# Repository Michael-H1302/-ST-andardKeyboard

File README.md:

A custom keyboard design made with KiCad. The Design uses a STM32 Blue Pill Microcontroller featuring red led backlight that can be controlled in three groups (two rows per group). Don't get confused by the name HotKeyBoard. I just made use of some previous work and derived it from an already existing KiCad project. 
The keyboard design supports standard mechanical switches like the Cherry MX and the Gateron. Due to the LED placement below the actual switch footprint, even switches without an
extra space for the LED are supported.

andardKeyboard.jpg)

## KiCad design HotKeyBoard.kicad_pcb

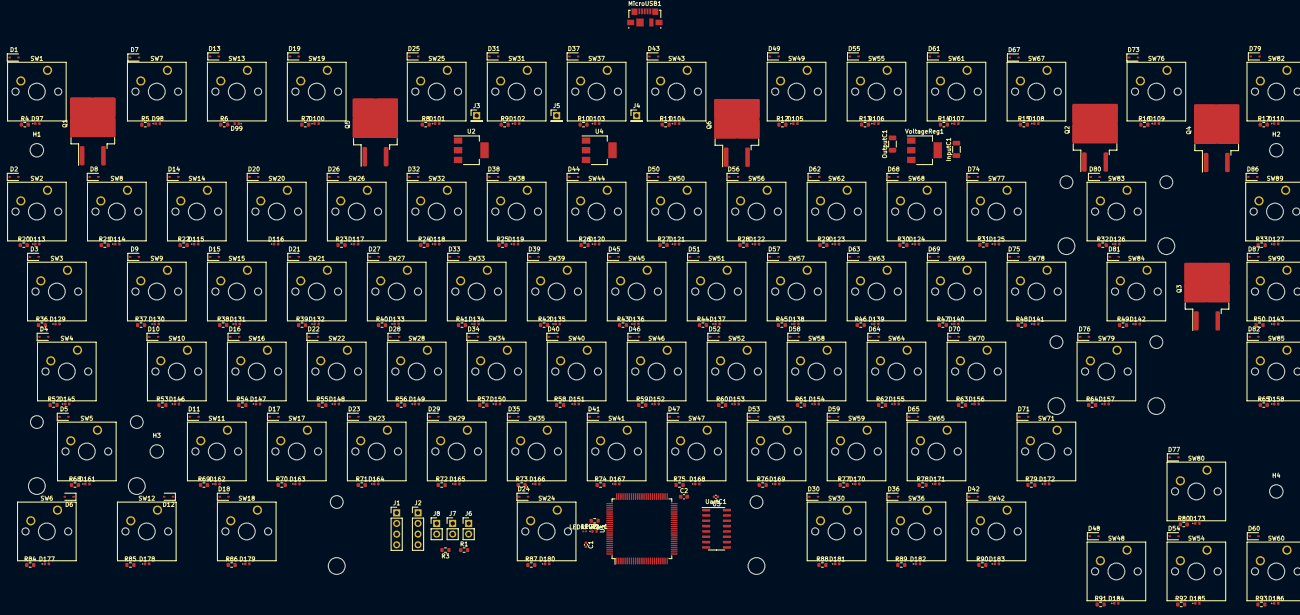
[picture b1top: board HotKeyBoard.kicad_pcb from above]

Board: 2 copper layers, 357 parts (0 on the bottom side), 211 nets, no tracks yet.

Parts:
C1: 0.1uF; C_0402_1005Metric
C2: 1uF; C_0603_1608Metric
D1, D2, D3, D4, D5, D6, D7, D8, D9, D10, D11, D12, D13, D14, D15, D16, D17, D18, D19, D20, D21, D22, D23, D24, D25, D26, D27, D28, D29, D30, D31, D32, D33, D34, D35, D36, D37, D38, D39, D40, D41, D42, D43, D44, D45, D46, D47, D48, D49, D50, D51, D52, D53, D54, D55, D56, D57, D58, D59, D60, D61, D62, D63, D64, D65, D67, D68, D69, D70, D71, D73, D74, D75, D76, D77, D79, D80, D81, D82, D86, D87: D; D_SOD-323
D97, D98, D99, D100, D101, D102, D103, D104, D105, D106, D107, D108, D109, D110, D113, D114, D115, D116, D117, D118, D119, D120, D121, D122, D123, D124, D125, D126, D127, D129, D130, D131, D132, D133, D134, D135, D136, D137, D138, D139, D140, D141, D142, D143, D145, D146, D147, D148, D149, D150, D151, D152, D153, D154, D155, D156, D157, D158, D161, D162, D163, D164, D165, D166, D167, D168, D169, D170, D171, D172, D173, D177, D178, D179, D180, D181, D182, D183, D184, D185, D186: LED; LED_0402_1005Metric
H1, H2, H3, H4: MountingHole; MountingHole_3.2mm_M3_DIN965
InputC1: 100uF; C_1206_3216Metric
J1, J2: Conn_01x04_Pin; PinHeader_1x04_P2.54mm_Vertical
J3: USB_VOLTAGE Measuring Point; PinHeader_1x01_P2.54mm_Vertical
J4: LED_VOLTAGE Measuring Point 1; PinHeader_1x01_P2.54mm_Vertical
J5: LED_VOLTAGE Measuring Point 2; PinHeader_1x01_P2.54mm_Vertical
J6, J7, J8: Conn_01x02_Pin; PinHeader_1x02_P2.54mm_Vertical
LEDPwr1: LED; LED_0402_1005Metric
LEDRPwr1: 65; R_0201_0603Metric
MicroUSB1: USB_OTG; USB_Micro-B_Molex_47346-0001
OutputC1: 100uF; C_1206_3216Metric
Q1, Q2, Q3, Q4, Q5, Q6: IRLZ34N; TO-263-2
R1, R2, R3: 10k; R_0603_1608Metric
R4, R5, R6, R7, R8, R9, R10, R11, R12, R13, R14, R15, R16, R17, R20, R21, R22, R23, R24, R25, R26, R27, R28, R29, R30, R31, R32, R33, R36, R37, R38, R39, R40, R41, R42, R43, R44, R45, R46, R47, R48, R49, R50, R52, R53, R54, R55, R56, R57, R58, R59, R60, R61, R62, R63, R64, R65, R68, R69, R70, R71, R72, R73, R74, R75, R76, R77, R78, R79, R80, R84, R85, R86, R87, R88, R89, R90, R91, R92, R93: R; R_0603_1608Metric
SW1, SW2, SW7, SW8, SW9, SW10, SW11, SW13, SW14, SW15, SW16, SW17, SW19, SW20, SW21, SW22, SW23, SW25, SW26, SW27, SW28, SW29, SW30, SW31, SW32, SW33, SW34, SW35, SW36, SW37, SW38, SW39, SW40, SW41, SW42, SW43, SW44, SW45, SW46, SW47, SW48, SW49, SW50, SW51, SW52, SW53, SW54, SW55, SW56, SW57, SW58, SW59, SW60, SW61, SW62, SW63, SW64, SW65, SW67, SW68, SW69, SW70, SW76, SW77, SW78, SW80, SW82, SW85, SW89, SW90: SW_Push; SW_Cherry_MX_1.00u_PCB
SW3, SW84: SW_Push; SW_Cherry_MX_1.50u_PCB
SW4, SW71: SW_Push; SW_Cherry_MX_1.75u_PCB
SW5, SW79: SW_Push; SW_Cherry_MX_2.25u_PCB
SW6, SW12, SW18: SW_Push; SW_Cherry_MX_1.25u_PCB
SW24: SW_Push; SW_Cherry_MX_6.25u_PCB
SW83: SW_Push; SW_Cherry_MX_2.00u_PCB
U1: STM32F103VBTx; LQFP-100_14x14mm_P0.5mm
U2, U4: AMS1117-3.3; SOT-223-3_TabPin2
U3: CH340C; SOIC-16_3.9x9.9mm_P1.27mm
UartC1: 0.1uF; C_0402_1005Metric
VoltageReg1: AMS1117-3.3; SOT-223-3_TabPin2

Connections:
3.3V: C1.2, C2.1, J1.4, J2.4, J7.1, LEDRPwr1.1, OutputC1.1, R1.1, R3.1, U1.6 (VBAT), U1.11 (VDD), U1.21 (VREF+), U1.22 (VDDA), U1.28 (VDD), U1.50 (VDD), U1.75 (VDD), U1.100 (VDD), U3.4 (V3), U3.16 (VCC), UartC1.2, VoltageReg1.2 (VO)
Boot0: J7.2, R2.1, U1.94 (BOOT0)
Boot1: J8.2, R3.2, U1.37 (PB2)
Col0: SW1.1, SW2.1, SW3.1, SW4.1, SW5.1, SW6.1, U1.81 (PD0)
Col1: SW7.1, SW8.1, SW9.1, SW10.1, SW11.1, SW12.1, U1.82 (PD1)
Col2: SW13.1, SW14.1, SW15.1, SW16.1, SW17.1, SW18.1, U1.83 (PD2)
Col3: SW19.1, SW20.1, SW21.1, SW22.1, SW23.1, SW24.1, U1.84 (PD3)
Col4: SW25.1, SW26.1, SW27.1, SW28.1, SW29.1, SW30.1, U1.85 (PD4)
Col5: SW31.1, SW32.1, SW33.1, SW34.1, SW35.1, SW36.1, U1.86 (PD5)
Col6: SW37.1, SW38.1, SW39.1, SW40.1, SW41.1, SW42.1, U1.87 (PD6)
Col7: SW43.1, SW44.1, SW45.1, SW46.1, SW47.1, SW48.1, U1.88 (PD7)
Col8: SW49.1, SW50.1, SW51.1, SW52.1, SW53.1, SW54.1, U1.55 (PD8)
Col9: SW55.1, SW56.1, SW57.1, SW58.1, SW59.1, SW60.1, U1.56 (PD9)
Col10: SW61.1, SW62.1, SW63.1, SW64.1, SW65.1, U1.57 (PD10)
Col11: SW67.1, SW68.1, SW69.1, SW70.1, SW71.1, U1.58 (PD11)
Col12: SW76.1, SW77.1, SW78.1, SW79.1, SW80.1, U1.59 (PD12)
Col13: SW82.1, SW83.1, SW84.1, SW85.1, U1.60 (PD13)
Col14: SW89.1, SW90.1, U1.61 (PD14)
D+: MicroUSB1.3 (D+), U1.71 (PA12), U3.5 (UD+)
D-: MicroUSB1.2 (D-), U1.70 (PA11), U3.6 (UD-)
GND: C1.1, C2.2, InputC1.2, J1.3, J2.1, J6.1, J8.1, LEDPwr1.1 (K), MicroUSB1.5 (GND), OutputC1.2, Q1.3 (S), Q2.3 (S), Q3.3 (S), Q4.3 (S), Q5.3 (S), Q6.3 (S), R2.2, U1.10 (VSS), U1.19 (VSSA), U1.20 (VREF-), U1.27 (VSS), U1.49 (VSS), U1.74 (VSS), U1.99 (VSS), U2.1 (GND), U3.1 (GND), U4.1 (GND), UartC1.1, VoltageReg1.1 (GND)
Gate0: Q1.1 (G), U1.89 (PB3)
Gate1: Q2.1 (G), U1.90 (PB4)
Gate2: Q3.1 (G), U1.91 (PB5)
Gate3: Q4.1 (G), U1.63 (PC6)
Gate4: Q5.1 (G), U1.64 (PC7)
Gate5: Q6.1 (G), U1.65 (PC8)
I2C_SCL: J1.2, U1.47 (PB10)
I2C_SDA: J1.1, U1.48 (PB11)
LED_INPUT_VOLTAGE1: J4.1, R4.1, R5.1, R6.1, R7.1, R8.1, R9.1, R10.1, R11.1, R12.1, R13.1, R14.1, R15.1, R16.1, R17.1, R20.1, R21.1, R22.1, R23.1, R24.1, R25.1, R26.1, R27.1, R28.1, R29.1, R30.1, R31.1, R32.1, R33.1, R36.1, R37.1, R38.1, R39.1, R40.1, R41.1, R42.1, R43.1, R44.1, R45.1, R46.1, R47.1, R48.1, R49.1, R50.1, U2.2 (VO)
LED_INPUT_VOLTAGE2: J5.1, R52.1, R53.1, R54.1, R55.1, R56.1, R57.1, R58.1, R59.1, R60.1, R61.1, R62.1, R63.1, R64.1, R65.1, R68.1, R69.1, R70.1, R71.1, R72.1, R73.1, R74.1, R75.1, R76.1, R77.1, R78.1, R79.1, R80.1, R84.1, R85.1, R86.1, R87.1, R88.1, R89.1, R90.1, R91.1, R92.1, R93.1, U4.2 (VO)
Mosfet0: D97.1 (K), D98.1 (K), D99.1 (K), D100.1 (K), D101.1 (K), D102.1 (K), D103.1 (K), D104.1 (K), D105.1 (K), D106.1 (K), D107.1 (K), D108.1 (K), D109.1 (K), D110.1 (K), Q1.2 (D)
Mosfet1: D113.1 (K), D114.1 (K), D115.1 (K), D116.1 (K), D117.1 (K), D118.1 (K), D119.1 (K), D120.1 (K), D121.1 (K), D122.1 (K), D123.1 (K), D124.1 (K), D125.1 (K), D126.1 (K), D127.1 (K), Q2.2 (D)
Mosfet2: D129.1 (K), D130.1 (K), D131.1 (K), D132.1 (K), D133.1 (K), D134.1 (K), D135.1 (K), D136.1 (K), D137.1 (K), D138.1 (K), D139.1 (K), D140.1 (K), D141.1 (K), D142.1 (K), D143.1 (K), Q3.2 (D)
Mosfet3: D145.1 (K), D146.1 (K), D147.1 (K), D148.1 (K), D149.1 (K), D150.1 (K), D151.1 (K), D152.1 (K), D153.1 (K), D154.1 (K), D155.1 (K), D156.1 (K), D157.1 (K), D158.1 (K), Q4.2 (D)
Mosfet4: D161.1 (K), D162.1 (K), D163.1 (K), D164.1 (K), D165.1 (K), D166.1 (K), D167.1 (K), D168.1 (K), D169.1 (K), D170.1 (K), D171.1 (K), D172.1 (K), D173.1 (K), Q5.2 (D)
Mosfet5: D177.1 (K), D178.1 (K), D179.1 (K), D180.1 (K), D181.1 (K), D182.1 (K), D183.1 (K), D184.1 (K), D185.1 (K), D186.1 (K), Q6.2 (D)
NRST: J6.2, R1.2, U1.14 (NRST)
unnamed: D1.2 (A), SW1.2
unnamed: D2.2 (A), SW2.2
unnamed: D3.2 (A), SW3.2
unnamed: D4.2 (A), SW4.2
unnamed: D5.2 (A), SW5.2
unnamed: D6.2 (A), SW6.2
unnamed: D7.2 (A), SW7.2
unnamed: D8.2 (A), SW8.2
unnamed: D9.2 (A), SW9.2
unnamed: D10.2 (A), SW10.2
unnamed: D11.2 (A), SW11.2
unnamed: D12.2 (A), SW12.2
unnamed: D13.2 (A), SW13.2
unnamed: D14.2 (A), SW14.2
unnamed: D15.2 (A), SW15.2
unnamed: D16.2 (A), SW16.2
unnamed: D17.2 (A), SW17.2
unnamed: D18.2 (A), SW18.2
unnamed: D19.2 (A), SW19.2
unnamed: D20.2 (A), SW20.2
unnamed: D21.2 (A), SW21.2
unnamed: D22.2 (A), SW22.2
unnamed: D23.2 (A), SW23.2
unnamed: D24.2 (A), SW24.2
unnamed: D25.2 (A), SW25.2
unnamed: D26.2 (A), SW26.2
unnamed: D27.2 (A), SW27.2
unnamed: D28.2 (A), SW28.2
unnamed: D29.2 (A), SW29.2
unnamed: D30.2 (A), SW30.2
unnamed: D31.2 (A), SW31.2
unnamed: D32.2 (A), SW32.2
unnamed: D33.2 (A), SW33.2
unnamed: D34.2 (A), SW34.2
unnamed: D35.2 (A), SW35.2
unnamed: D36.2 (A), SW36.2
unnamed: D37.2 (A), SW37.2
unnamed: D38.2 (A), SW38.2
unnamed: D39.2 (A), SW39.2
unnamed: D40.2 (A), SW40.2
unnamed: D41.2 (A), SW41.2
unnamed: D42.2 (A), SW42.2
unnamed: D43.2 (A), SW43.2
unnamed: D44.2 (A), SW44.2
unnamed: D45.2 (A), SW45.2
unnamed: D46.2 (A), SW46.2
unnamed: D47.2 (A), SW47.2
unnamed: D48.2 (A), SW48.2
unnamed: D49.2 (A), SW49.2
unnamed: D50.2 (A), SW50.2
unnamed: D51.2 (A), SW51.2
unnamed: D52.2 (A), SW52.2
unnamed: D53.2 (A), SW53.2
unnamed: D54.2 (A), SW54.2
unnamed: D55.2 (A), SW55.2
unnamed: D56.2 (A), SW56.2
unnamed: D57.2 (A), SW57.2
unnamed: D58.2 (A), SW58.2
unnamed: D59.2 (A), SW59.2
unnamed: D60.2 (A), SW60.2
unnamed: D61.2 (A), SW61.2
unnamed: D62.2 (A), SW62.2
unnamed: D63.2 (A), SW63.2
unnamed: D64.2 (A), SW64.2
unnamed: D65.2 (A), SW65.2
unnamed: D67.2 (A), SW67.2
unnamed: D68.2 (A), SW68.2
unnamed: D69.2 (A), SW69.2
unnamed: D70.2 (A), SW70.2
unnamed: D71.2 (A), SW71.2
unnamed: D73.2 (A), SW76.2
unnamed: D74.2 (A), SW77.2
unnamed: D75.2 (A), SW78.2
unnamed: D76.2 (A), SW79.2
unnamed: D77.2 (A), SW80.2
unnamed: D79.2 (A), SW82.2
unnamed: D80.2 (A), SW83.2
unnamed: D81.2 (A), SW84.2
unnamed: D82.2 (A), SW85.2
unnamed: D86.2 (A), SW89.2
unnamed: D87.2 (A), SW90.2
unnamed: D97.2 (A), R4.2
unnamed: D98.2 (A), R5.2
unnamed: D99.2 (A), R6.2
unnamed: D100.2 (A), R7.2
unnamed: D101.2 (A), R8.2
unnamed: D102.2 (A), R9.2
unnamed: D103.2 (A), R10.2
unnamed: D104.2 (A), R11.2
unnamed: D105.2 (A), R12.2
unnamed: D106.2 (A), R13.2
unnamed: D107.2 (A), R14.2
unnamed: D108.2 (A), R15.2
unnamed: D109.2 (A), R16.2
unnamed: D110.2 (A), R17.2
unnamed: D113.2 (A), R20.2
unnamed: D114.2 (A), R21.2
unnamed: D115.2 (A), R22.2
unnamed: D116.2 (A), R23.2
unnamed: D117.2 (A), R24.2
unnamed: D118.2 (A), R25.2
unnamed: D119.2 (A), R26.2
unnamed: D120.2 (A), R27.2
unnamed: D121.2 (A), R28.2
unnamed: D122.2 (A), R29.2
unnamed: D123.2 (A), R30.2
unnamed: D124.2 (A), R31.2
unnamed: D125.2 (A), R32.2
unnamed: D126.2 (A), R33.2
unnamed: D129.2 (A), R36.2
unnamed: D130.2 (A), R37.2
unnamed: D131.2 (A), R38.2
unnamed: D132.2 (A), R39.2
unnamed: D133.2 (A), R40.2
unnamed: D134.2 (A), R41.2
unnamed: D135.2 (A), R42.2
unnamed: D136.2 (A), R43.2
unnamed: D137.2 (A), R44.2
unnamed: D138.2 (A), R45.2
unnamed: D139.2 (A), R46.2
unnamed: D140.2 (A), R47.2
unnamed: D141.2 (A), R48.2
unnamed: D142.2 (A), R49.2
unnamed: D143.2 (A), R50.2
unnamed: D145.2 (A), R52.2
unnamed: D146.2 (A), R53.2
unnamed: D147.2 (A), R54.2
unnamed: D148.2 (A), R55.2
unnamed: D149.2 (A), R56.2
unnamed: D150.2 (A), R57.2
unnamed: D151.2 (A), R58.2
unnamed: D152.2 (A), R59.2
unnamed: D153.2 (A), R60.2
unnamed: D154.2 (A), R61.2
unnamed: D155.2 (A), R62.2
unnamed: D156.2 (A), R63.2
unnamed: D157.2 (A), R64.2
unnamed: D158.2 (A), R65.2
unnamed: D161.2 (A), R68.2
unnamed: D162.2 (A), R69.2
unnamed: D163.2 (A), R70.2
unnamed: D164.2 (A), R71.2
unnamed: D165.2 (A), R72.2
unnamed: D166.2 (A), R73.2
unnamed: D167.2 (A), R74.2
unnamed: D168.2 (A), R75.2
unnamed: D169.2 (A), R76.2
unnamed: D170.2 (A), R77.2
unnamed: D171.2 (A), R78.2
unnamed: D172.2 (A), R79.2
unnamed: D173.2 (A), R80.2
unnamed: D177.2 (A), R84.2
unnamed: D178.2 (A), R85.2
unnamed: D179.2 (A), R86.2
unnamed: D180.2 (A), R87.2
unnamed: D181.2 (A), R88.2
unnamed: D182.2 (A), R89.2
unnamed: D183.2 (A), R90.2
unnamed: D184.2 (A), R91.2
unnamed: D185.2 (A), R92.2
unnamed: D186.2 (A), R93.2
unnamed: LEDPwr1.2 (A), LEDRPwr1.2
RX: U1.68 (PA9), U3.3 (RXD)
Row0: D1.1 (K), D7.1 (K), D13.1 (K), D19.1 (K), D25.1 (K), D31.1 (K), D37.1 (K), D43.1 (K), D49.1 (K), D55.1 (K), D61.1 (K), D67.1 (K), D73.1 (K), D79.1 (K), U1.97 (PE0)
Row1: D2.1 (K), D8.1 (K), D14.1 (K), D20.1 (K), D26.1 (K), D32.1 (K), D38.1 (K), D44.1 (K), D50.1 (K), D56.1 (K), D62.1 (K), D68.1 (K), D74.1 (K), D80.1 (K), D86.1 (K), U1.98 (PE1)
Row2: D3.1 (K), D9.1 (K), D15.1 (K), D21.1 (K), D27.1 (K), D33.1 (K), D39.1 (K), D45.1 (K), D51.1 (K), D57.1 (K), D63.1 (K), D69.1 (K), D75.1 (K), D81.1 (K), D87.1 (K), U1.1 (PE2)
Row3: D4.1 (K), D10.1 (K), D16.1 (K), D22.1 (K), D28.1 (K), D34.1 (K), D40.1 (K), D46.1 (K), D52.1 (K), D58.1 (K), D64.1 (K), D70.1 (K), D76.1 (K), D82.1 (K), U1.2 (PE3)
Row4: D5.1 (K), D11.1 (K), D17.1 (K), D23.1 (K), D29.1 (K), D35.1 (K), D41.1 (K), D47.1 (K), D53.1 (K), D59.1 (K), D65.1 (K), D71.1 (K), D77.1 (K), U1.3 (PE4)
Row5: D6.1 (K), D12.1 (K), D18.1 (K), D24.1 (K), D30.1 (K), D36.1 (K), D42.1 (K), D48.1 (K), D54.1 (K), D60.1 (K), U1.4 (PE5)
SWCLK: J2.2, U1.76 (PA14)
SWDIO: J2.3, U1.72 (PA13)
TX: U1.69 (PA10), U3.2 (TXD)
USB_VOLT: InputC1.1, J3.1, MicroUSB1.1 (VBUS), U2.3 (VI), U4.3 (VI), VoltageReg1.3 (VI)

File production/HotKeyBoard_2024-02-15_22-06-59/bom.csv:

Designator,Footprint,Quantity,Value,LCSC Part #
"D1, D10, D100, D101, D102, D103, D104, D105, D106, D107, D108, D109, D11, D110, D111, D112, D113, D114, D115, D116, D117, D118, D119, D12, D120, D121, D122, D123, D124, D125, D126, D127, D128, D129, D13, D130, D131, D132, D133, D134, D135, D136, D137, D138, D139, D14, D140, D141, D142, D143, D144, D15, D16, D17, D18, D19, D2, D20, D21, D22, D23, D24, D25, D26, D27, D28, D29, D3, D30, D31, D32, D33, D34, D35, D36, D37, D38, D39, D4, D40, D41, D42, D43, D44, D45, D46, D47, D48, D49, D5, D50, D51, D52, D53, D54, D55, D56, D57, D58, D59, D6, D60, D61, D62, D63, D64, D65, D66, D67, D68, D69, D7, D70, D71, D72, D73, D74, D75, D76, D77, D78, D79, D8, D80, D81, D82, D83, D84, D85, D86, D87, D88, D89, D9, D90, D91, D92, D93, D94, D95, D96, D97, D98, D99",D_SOD-323,144,D,
"J1, J2",PinHeader_1x12_P2.54mm_Vertical,2,Conn_01x12_Socket,
"SW1, SW10, SW11, SW12, SW13, SW14, SW15, SW16, SW17, SW18, SW19, SW2, SW20, SW21, SW22, SW23, SW24, SW25, SW26, SW27, SW28, SW29, SW3, SW30, SW31, SW32, SW33, SW34, SW35, SW36, SW37, SW38, SW39, SW4, SW40, SW41, SW42, SW43, SW44, SW45, SW46, SW47, SW48, SW5, SW53, SW54, SW55, SW56, SW57, SW58, SW59, SW6, SW60, SW61, SW65, SW7, SW70, SW71, SW72, SW8, SW9",SW_Cherry_MX_1.00u_PCB,61,SW_Push,
"SW49, SW50, SW51",SW_Cherry_MX_1.25u_PCB,3,SW_Push,
SW52,SW_Cherry_MX_6.25u_PCB,1,SW_Push,
"SW62, SW67",SW_Cherry_MX_1.50u_PCB,2,SW_Push,
"SW63, SW69",SW_Cherry_MX_1.75u_PCB,2,SW_Push,
"SW64, SW68",SW_Cherry_MX_2.25u_PCB,2,SW_Push,
SW66,SW_Cherry_MX_2.00u_PCB,1,SW_Push,

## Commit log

2024-02-11 Inital layout
2024-02-15 Moved function key
2024-02-16 Changed to 75 layout without function row, but added makro column instead
2024-02-16 Added mounting holes
2024-03-02 Fixed bug in keyboard matrix
2024-03-02 Fixed matrix design
2024-03-11 Final production layout
2024-03-15 Added keyboard firmware
2024-03-15 Updated firmware
2024-03-15 Started doing the schematic
2024-03-16 Finished schematic
2024-03-16 Started layout
2024-03-17 Continued layout, deleted firmware
2024-03-23 Finished single sided layout
2024-04-10 Added overbridging of mosfets
2024-04-10 Added THT micro usb
2024-04-11 Changed micro usb port
2024-04-12 Switched micro usb again
2024-04-20 Finished layout
2024-04-20 Fixed resistor
2024-04-21 Added multiple mosfets
2024-04-21 Rewired leds
2024-04-21 Changed led resistor to smaller value to give pwm control more range to play with
2024-04-22 Increased track width for led power delivery
2024-04-22 Moved some labels
2024-04-23 Added 0ohm resistor before the last led row in order to be able to turn it off
2024-07-02 Added name and version to the pcb
2024-09-23 Fixed some layout issues with a single misplaced led and the resistor for disabling the last led row
